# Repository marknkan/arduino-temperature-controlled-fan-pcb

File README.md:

# Arduino Temperature-Controlled Fan PCB

My first manufactured PCB: an Arduino Uno expansion board for a temperature-controlled DC fan with automatic and manual operating modes.

This project developed an earlier breadboard prototype into my first manufactured PCB. It brought together embedded programming, analogue sensing, PWM motor control, user inputs, LCD output, schematic capture, PCB layout, soldering, testing and hardware debugging.

Arduino Uno, Embedded C/C++, KiCad, PCB Design, PWM ADC, and Hardware Debugging

Status — Version 1 tested: The PCB was successfully designed, manufactured and assembled. The controls and several interfaces worked, while bring-up exposed three hardware issues to correct in Version 2: the fan-driver routing, RGB LED pin mapping and LM35 interface

[Powered assembled PCB](docs/images/hardware/pcb-powered-on.jpg)

[Watch the Version 1 prototype demonstration] (https://github.com/marknkan/arduino-temperature-controlled-fan-pcb/releases/tag/v1.0)

# Contents

- Project objectives

- Operating modes

- Hardware

- Main pin assignments

- PCB development

### Schematic

### PCB layout

### 3D render

- Firmware development

- Testing and results

- Detailed engineering test log

# What I learned

- Version 2 improvements

- Repository structure

- Project objectives

- Convert a working breadboard fan controller into a custom PCB.

- Read temperature using an LM35 analogue temperature sensor.

- Control a DC fan automatically according to temperature.

- Provide manual fan-speed control using a potentiometer.

- Display the selected mode, temperature and fan output on a 16×2 LCD.

- Use of an RGB LED to indicate operating mode and temperature range.

- Use of push buttons to change mode and return to the startup screen.

- Complete the full PCB lifecycle from schematic capture to assembly and testing.

# Operating modes

- Automatic mode

The Arduino reads the LM35 sensor and changes the requested fan speed and RGB status according to temperature:

| Temperature | Fan command | RGB indicator |
| :--- | :--- | :--- |
| Below 20 °C | Low | Blue |
| 20–28 °C | Medium | Orange/amber |
| Above 28 °C | Full | Red |

# Manual mode

The potentiometer is read through an analogue input and mapped to a PWM value from 0–255. This value controls the requested fan speed, the green LED brightness and the fan percentage shown on the LCD.

- Hardware

- Arduino Uno R3

- Custom two-layer PCB

- LM35 temperature sensor

- 16×2 HD44780-compatible LCD

- Common-cathode RGB LED and current-limiting resistors

- DC fan

- NPN transistor motor-driver stage

- Flyback diode

- Motor suppression capacitor

- Potentiometer

- Two push buttons

- External battery supply

- Screw terminals and Arduino stacking headers

# Main pin assignments

| Function | Arduino pin |
| :--- | :--- |
| Mode button | D2 |
| LCD RS | D3 |
| LCD Enable | D4 |
| LCD D4 | D5 |
| RGB blue | D6 |
| LCD D5 | D7 |
| LCD D6 | D8 |
| RGB red/green channels | D9 and D10 |
| Fan PWM command | D11 |
| LCD D7 | D12 |
| Reset/startup button | D13 |
| LM35 output | A0 |
| Potentiometer | A4 |

# Revision note:
Early firmware used A5 for the LM35 before PCB testing moved it to A0. The red and green RGB assignments were also swapped between D9 and D10 during diagnosis. These changes are retained in the test history below.

# PCB development
1. PCB development

2. The board was designed in KiCad. The workflow included:

3. Schematic capture and net labelling

4. Electrical Rules Check (ERC)

5. Through-hole footprint selection

6. Component placement and board-outline creation

7. Track routing and ground-zone fills

8. Design Rules Check (DRC)

9. Gerber and drill-file generation

10. PCB manufacture

11. Through-hole assembly and soldering

12. Continuity, voltage and functional testing

The manufactured board had a clean finish, readable silkscreen and correctly aligned Arduino headers.

# Firmware development

The firmware was changed throughout bring-up so individual subsystems could be isolated and tested.

| Stage | Code change | Reason and result |
| :--- | :--- | :--- |
| Initial controller | Added automatic and manual modes, Serial selection at 9600 baud, LM35 conversion and PWM fan control | Established the working breadboard behaviour before PCB integration. |
| LCD integration | Added LiquidCrystal lcd(3, 4, 5, 7, 8, 12) and lcd.begin(16, 2) | Displayed startup, selected mode, temperature and manual speed percentage. |
| Input handling | Configured buttons D2 and D13 with active-LOW logic and a 300 ms debounce/reset delay | Enabled mode switching and return to the startup screen. |
| Manual control | Mapped potentiometer 0–1023 to PWM 0–255, then to 0–100% for the LCD | Potentiometer readings changed correctly and the manual control logic worked. |
| Automatic control | Set fan commands to 80, 180 and 255 at <20 °C, 20–28 °C and >28 °C | Preserved the three temperature bands from the breadboard system. |
| Sensor debugging | Changed the LM35 input from A5 to A0 and printed raw ADC, calculated voltage and temperature | Exposed abnormal sensor values instead of hiding them behind the temperature calculation. |
| RGB debugging | Swapped red/green assignments between D10/D9 and D9/D10; ran individual colour tests | Red and green responded, but blue remained open because of the hardware pin-order mismatch. |
| Timing adjustments | Tried 1000 ms and 1200 ms automatic delays; retained a 250 ms manual delay | Made Serial and LCD behaviour easier to observe during testing. |
| Safe reset | Set fan PWM to 0 and requested RGB white 255,255,255 before returning to startup | Fan-off logic worked in code; true white was prevented by the failed blue LED channel. |

The final repository should retain the complete Arduino source in firmware/ so the implementation can be compared with this change history.

# Testing and Results 

| Area | Result | Notes |
| :--- | :--- | :--- |
| PCB manufacture | Pass | Board quality, outline, silkscreen and header alignment were good. |
| Arduino connection | Pass | The PCB fitted and connected to the Arduino Uno through its headers. |
| Power and continuity | Pass | Key power and signal connections were checked before full testing. |
| Push buttons | Pass | Mode selection and startup/reset input were detected. |
| Potentiometer input | Pass | The analogue value changed correctly. |
| LCD interface | Partial | The display powered up, but contrast and signal problems prevented reliable text. |
| LM35 circuit | Partial | The circuit produced inconsistent analogue readings during orientation and soldering tests. |
| RGB LED | Partial | Red and green worked; a footprint-to-component mismatch prevented blue. |
| Fan-driver stage | Fail — V1 | The transistor emitter and collector were routed incorrectly for the intended low-side switch. |

# Debugging performed

- Used continuity mode to trace PCB nets and verify solder joints.

- Measured supply and analogue voltages with a multimeter.

- Checked the Arduino headers and LCD signal paths.

- Investigated LCD power, contrast and data connections.

- Removed, reoriented and resoldered the LM35 during sensor testing.

- Tested individual RGB LED channels and identified a footprint/pinout mismatch.

- Reviewed the transistor circuit and found the emitter/collector routing error.

- Reflowed joints and used solder wick and a solder sucker where required.

# Detailed engineering test log

This section preserves the numerical readings and different troubleshooting approaches used during Version 1 bring-up. Conflicting results are intentionally included because they were recorded at different stages of debugging.

<details>
<summary><strong>View detailed test measurements and troubleshooting log</strong></summary>

# Test equipment and reference values

| Item | Value or setting | Purpose |
| :--- | :--- | :--- |
| Multimeter | Continuity/resistance mode | Checking tracks, headers, solder joints and component paths |
| Multimeter | 20 V DC range | Measuring the Arduino, LCD, LM35 and PCB supply voltages |
| Arduino ADC | 10-bit, 0–1023 | Reading the LM35 and potentiometer |
| ADC reference used in firmware | 5.0 V | Converting ADC counts to voltage |
| LM35 scale factor | 10 mV/°C | Converting sensor output voltage to temperature |
| Expected LM35 room-temperature output | Approximately 0.18–0.30 V | Reference range used during diagnosis |
| Serial Monitor | 9600 baud | Viewing raw ADC, voltage, temperature and potentiometer data |
| LCD | 16 columns × 2 rows | User display |

The conversion used in the firmware was:

voltage = rawADC × (5.0 / 1023.0)
temperatureC = voltage × 100.0

An earlier temperature-monitor version expressed the same conversion as:

voltage = (5.0 / 1023.0) × rawADC
millivolts = voltage × 1000
temperatureC = millivolts / 10

# Firmware values tested

| Parameter | Value |
| :--- | :--- |
| Full fan PWM | 255 |
| Medium fan PWM | 180 |
| Low fan PWM | 80 |
| Fan off PWM | 0 |
| Full LED brightness | 255 |
| Potentiometer ADC input range | 0–1023 |
| Mapped manual PWM range | 0–255 |
| Mapped LCD speed range | 0–100% |
| Cold threshold | <20 °C |
| Medium-temperature range | 20–28 °C |
| Hot threshold | >28 °C |
| Amber RGB command | Red 255, Green 40, Blue 0 |
| Reset/startup RGB command | Red 255, Green 255, Blue 255 |
| Automatic-loop delays tried | 1000 ms and 1200 ms |
| Manual-loop delay | 250 ms |
| Button debounce/reset delay | 300 ms |

# LCD tests

| Test or observation | Result |
| :--- | :--- |
| LCD interface tested with LiquidCrystal lcd(3, 4, 5, 7, 8, 12) | This was the final PCB-oriented firmware mapping: RS=D3, E=D4, D4=D5, D5=D7, D6=D8, D7=D12. |
| LCD supply/header continuity | Recorded readings across tested LCD signal paths were approximately 0–0.8 Ω, supporting continuity through the PCB connections. |
| LCD power-up | The backlight powered and white character blocks appeared, showing that the module had power but was not displaying valid text. |
| Firmware/serial activity | The display later flickered in time with Serial activity. It also became dim and flashed during later attempts. |
| Contrast pin approach | LCD pin 3 (VO) was investigated because no dedicated contrast potentiometer was fitted to the PCB. |
| Temporary contrast tests proposed | VO directly to GND or through approximately 1 kΩ; these were diagnostic approaches and were not preserved as confirmed final measurements. |
| LCD power reference used for diagnosis | Pin 1=GND, pin 2=5 V, pin 5 (RW)=GND, pin 15=5 V, pin 16=GND. |
| Startup text in firmware | Line 1: Auto or Manual?; line 2: Pick :). |
| Mode screens in firmware | (Automatic Mode) with Degrees (C):; (Manual Mode) with Speed: <0–100>%. |

# LM35 temperature-sensor tests

| Test stage | Recorded result | Interpretation/action |
| :--- | :--- | :--- |
| Original PCB definition | LM35-LP U1, TO-92_Inline; Pad 1=+5 V, Pad 2=VOUT, Pad 3=GND | The footprint’s flat-face edge was shown at the bottom, creating an orientation check against the real part. |
| Firmware revisions | Early versions used A5; later PCB testing used A0 | This A5/A0 mismatch was tracked as a firmware/documentation conflict. |
| First abnormal result | Approximately 70 °C | Far above room temperature, so the sensor orientation, pin mapping, soldering and ADC input were investigated. |
| Later abnormal result | Approximately 200 °C | Confirmed that the analogue signal was still invalid rather than representing room temperature. |
| Serial debug result | Raw ADC=471 | Used to calculate the corresponding input voltage. |
| Calculated ADC voltage | 471 × (5/1023) = 2.302 V | Much higher than the expected LM35 room-temperature output. |
| Calculated temperature | 2.302 V × 100 = 230.2 °C | Demonstrated that the code conversion was consistent with the voltage, but the input signal was incorrect. |
| Later A0 measurement | Approximately 0.03 V | Too low for the expected room-temperature LM35 output. |
| LM35 middle/output pin measurement | Approximately 1.25 V | Equivalent to roughly 125 °C using the LM35 scale; still invalid for room temperature. |
| Nearby header/supply-gap measurement | Approximately 4.67 V | Confirmed that a near-5 V supply was present at the tested header location. |
| Expected room-temperature reference | Approximately 0.18–0.30 V | Equivalent to roughly 18–30 °C. None of the abnormal readings consistently matched this range. |
| Sensor installed | Arduino sometimes appeared as COM9 | The sensor’s presence coincided with a changed/unstable port during one stage of testing. |
| Sensor removed | Arduino appeared as COM11 | Removing the LM35 restored the expected connection during that attempt. |
| After removal/resoldering | COM11 operation later returned | The COM-port issue was eventually cleared, but the sensor output remained unreliable. |
| Orientation attempt | LM35 was removed, flipped/reoriented and soldered again | The same general fault remained, reducing confidence that orientation alone was the cause. |
| Replacement approach | A bare LM35 was tried | This ruled out relying only on the original sensor/component form. |
| Hole-clearing issue | Desoldered holes filled with solder | Wick/sucker and reheating were used until the sensor could be inserted again. |
| Unsoldered insertion test | LM35 could be inserted after the holes were cleared | Used as another contact/orientation test before final soldering. |

The usual LM35 TO-92 reference used during diagnosis, with the flat face toward the viewer, was:

Left: +5 V    Middle: VOUT    Right: GND

This was checked against the exact part and PCB footprint rather than assumed to be universally correct.

# RGB LED tests

| Test or observation | Result |
| :--- | :--- |
| Physical LED type | 5 mm diffused common-cathode RGB LED |
| Physical orientation observed | Flat side facing right; longest lead expected to be the common cathode/GND. |
| PCB pad order | Pad 1=Red, Pad 2=Green, Pad 3=Blue, Pad 4=GND |
| Suspected physical LED order | Red, Green, GND, Blue |
| Red-channel continuity/function | Continuity/function was obtained. |
| Green-channel continuity/function | Continuity/function was obtained. |
| Blue-channel continuity test | OL / open circuit was observed. |
| Visual functional result | Red and green worked; blue did not. White, which requires all three channels, therefore could not display correctly. |
| Earlier firmware mapping | Red=D10, Green=D9, Blue=D6 |
| Later test mapping | Red=D9, Green=D10, Blue=D6 |
| Manual-mode target | Green brightness follows the potentiometer PWM value from 0–255. |
| Automatic-mode target | Blue below 20 °C; amber from 20–28 °C; red above 28 °C. |
| Mechanical inspection | Bent/soldered LED leads were checked because adjacent pins might have touched. |
| Diagnostic approaches | Individual-channel sketches, red/green pin swapping, reflowing solder joints and continuity tests through the resistors/tracks were used. |

# Potentiometer and button tests

| Test | Result |
| :--- | :--- |
| Potentiometer input | Connected to A4; ADC range 0–1023 was mapped to PWM 0–255. |
| LCD manual output | PWM 0–255 was mapped again to 0–100%. |
| Potentiometer hardware | The physical potentiometer did not match the selected footprint cleanly and was trimmed/adjusted to fit. |
| Potentiometer response | Analogue values changed, confirming that the control input worked. |
| Mode button | D2, configured with INPUT_PULLUP; active state=LOW. |
| Second/reset button | D13, active state=LOW. |
| Mode action | Toggled the manualMode Boolean after a 300 ms debounce delay in one firmware version. |
| Reset action | Set fan PWM to 0, commanded RGB 255,255,255, waited 300 ms, and returned to the startup selection. |
| Functional result | Both mode/reset button functions were detected during testing. |

# Motor, transistor and power tests

| Test or design review | Result |
| :--- | :--- |
| Motor PWM pin | Arduino D11 |
| Intended driver | 2N2222 NPN low-side switch |
| Intended power path | Battery positive → fan positive; fan negative → transistor collector; transistor emitter → GND/battery negative |
| Intended control path | Arduino D11 → base resistor → transistor base |
| Grounding requirement | Arduino GND and external battery negative must share a common ground. |
| Supplies considered/tried | Initially a 9 V battery; later a switched 4×AA battery holder with rechargeable cells. |
| Fan command values | Off=0, low=80, medium=180, full=255 |
| Terminal inspection | Fan/battery wires were found loose in the screw terminals during bring-up and required reseating/tug checking. |
| Driver design review | The PCB emitter/collector routing did not implement the intended low-side switch correctly. |
| Functional result | The V1 fan-driver stage did not operate successfully from the assembled PCB. |
| Conclusion | Because the copper routing was wrong, repeated firmware changes could not correct the hardware fault. |

# Arduino and PCB interconnection tests

| Test | Result |
| :--- | :--- |
| Arduino stacking headers | Soldered and the PCB was fitted directly onto the Arduino Uno. |
| Header alignment | Mechanically aligned with the Uno and the manufactured board fitted successfully. |
| Power-up | Board and LCD received power without an immediate destructive failure. |
| Continuity testing | Used across LCD nets, RGB resistors/tracks, ground paths and header connections. |
| Solder repair methods | Joint reflow, added flux, solder wick, solder sucker and hole clearing. |
| KiCad checks before manufacture | ERC and DRC completed; the PCB update reported 0 warnings and 0 errors. |
| Key lesson | 0 ERC/DRC errors confirmed rule compliance, but did not detect incorrect real-component pin mapping or the transistor circuit-design error. |

# Approaches discussed but not recorded as completed measurements

The following were valid troubleshooting proposals, but no final numerical result was preserved. They are separated to avoid presenting suggestions as measured evidence:

- Testing LCD VO directly at GND and through approximately 1 kΩ.

- Confirming every LCD supply pin with an exact 5.00 V measurement.

- Testing the fan independently by connecting it directly to the external battery.

- Measuring transistor base, collector and emitter voltages while commanding PWM 0 and 255.

- Testing each RGB colour with a standalone current-limited supply.

- Rebuilding the LM35 circuit fully on a breadboard and comparing its output with the PCB.

- Substituting another known-good LM35 and repeating the same voltage measurements.

</details>

# What I learned

- How to move from a breadboard prototype to a manufactured PCB.

- How schematic symbols, footprints and real component pinouts must be verified against datasheets.

- How to use ERC and DRC without treating a clean result as proof that the circuit itself is correct.

- How an NPN transistor should be connected as a low-side motor switch.

- Why component orientation, test points and accessible connectors matter during bring-up.

- How to perform staged power-up, continuity and voltage testing.

- How hardware faults can appear to be software faults, and vice versa.

- How to document failed tests and turn them into specific design changes.

# Version 2 improvements

- Correct the transistor emitter/collector routing.

- Verify every symbol-to-footprint pin mapping against the component datasheet.

- Use an RGB LED footprint that matches the exact physical pin order.

- Add a socket or removable header for the LM35.

- Improve LCD contrast control and connector labelling.

- Add clearly labelled test points for power, ground, sensor output and PWM.

- Improve component spacing and keep parts farther from the board edge.

- Review motor-current requirements and select the driver stage accordingly.

- Repeat schematic peer review, ERC, DRC and bench validation before manufacture.
├── firmware/          # Arduino source code
├── hardware/
│   ├── kicad/         # KiCad schematic and PCB files
│   ├── gerbers/       # PCB manufacturing files
│   └── bom/           # Bill of materials
├── docs/
│   ├── images/        # Project and testing photographs
│   └── testing/       # Measurements and test notes
├── LICENSE
└── README.md

# Author
# Mark Nkan
- Electrical and Electronic Engineering student interested in embedded systems, PCB design, control systems and hardware development.

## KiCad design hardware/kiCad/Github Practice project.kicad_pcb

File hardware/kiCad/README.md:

# KiCad Design Files

This folder contains the schematic and PCB-layout source files for the Arduino temperature-controlled fan controller.

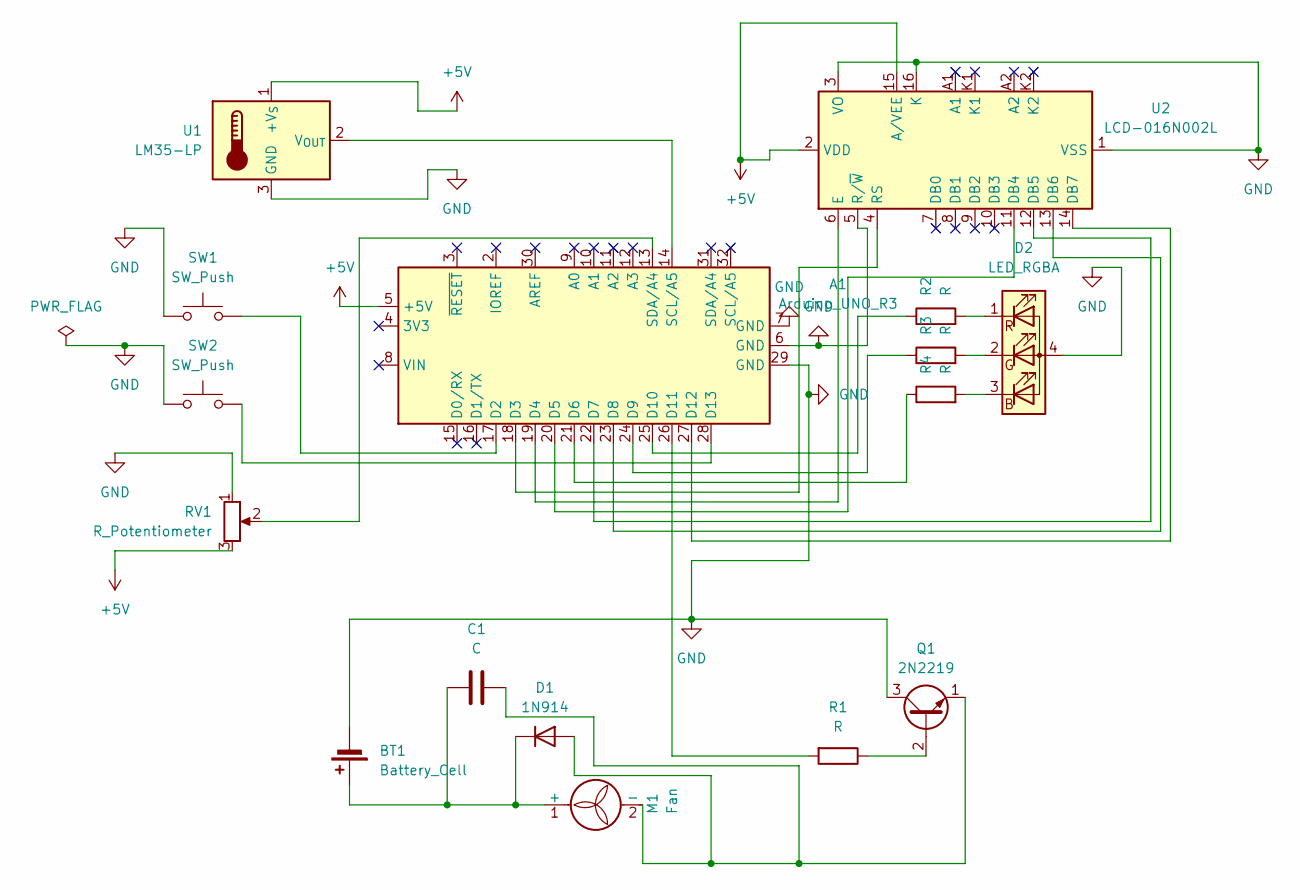
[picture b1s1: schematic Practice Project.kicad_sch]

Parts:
A1: Arduino_UNO_R3
BT1: Battery_Cell; TerminalBlock_MaiXu_MX126-5.0-02P_1x02_P5.00mm
C1: C; C_Disc_D5.0mm_W2.5mm_P2.50mm
D1: 1N914; D_DO-35_SOD27_P7.62mm_Horizontal
D2: LED_RGBA; PinHeader_1x04_P2.54mm_Vertical
M1: Fan; TerminalBlock_MaiXu_MX126-5.0-02P_1x02_P5.00mm
Q1: 2N2219; TO-39-3
R1, R2, R3, R4: R; R_Axial_DIN0207_L6.3mm_D2.5mm_P7.62mm_Horizontal
RV1: R_Potentiometer; TerminalBlock_MaiXu_MX126-5.0-03P_1x03_P5.00mm
SW1, SW2: SW_Push; SW_PUSH_6mm
U1: LM35-LP; TO-92_Inline
U2: LCD-016N002L

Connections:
+5V: A1.5 (+5V), RV1.3, U1.1 (+V_{S}), U2.2 (VDD), U2.15 (A/VEE)
GND: A1.6 (GND), A1.7 (GND), A1.29 (GND), BT1.2 (-), D2.4 (A), Q1.3 (C), RV1.1, SW1.1, SW2.1, U1.3 (GND), U2.1 (VSS), U2.3 (VO), U2.5 (R/~W), U2.16 (K)
unnamed: A1.17 (D2), SW1.2
unnamed: A1.18 (D3), U2.4 (RS)
unnamed: A1.19 (D4), U2.6 (E)
unnamed: A1.20 (D5), U2.11 (DB4)
unnamed: A1.21 (D6), R4.1
unnamed: A1.22 (D7), U2.12 (DB5)
unnamed: A1.23 (D8), U2.13 (DB6)
unnamed: A1.24 (D9), R3.1
unnamed: A1.25 (D10), R2.1
unnamed: A1.26 (D11), R1.2
unnamed: A1.27 (D12), U2.14 (DB7)
unnamed: A1.28 (D13), SW2.2
unnamed: A1.13 (SDA/A4), RV1.2
unnamed: BT1.1 (+), C1.1, D1.1 (K), M1.1 (+)
unnamed: C1.2, D1.2 (A), M1.2 (-), Q1.1 (E)
unnamed: D2.3 (BK), R4.2
unnamed: D2.2 (GK), R3.2
unnamed: D2.1 (RK), R2.2
unnamed: Q1.2 (B), R1.1
unnamed: A1.14 (SCL/A5), U1.2 (V_{OUT})

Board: 2 copper layers, 16 parts (0 on the bottom side), 22 nets, no tracks yet.
